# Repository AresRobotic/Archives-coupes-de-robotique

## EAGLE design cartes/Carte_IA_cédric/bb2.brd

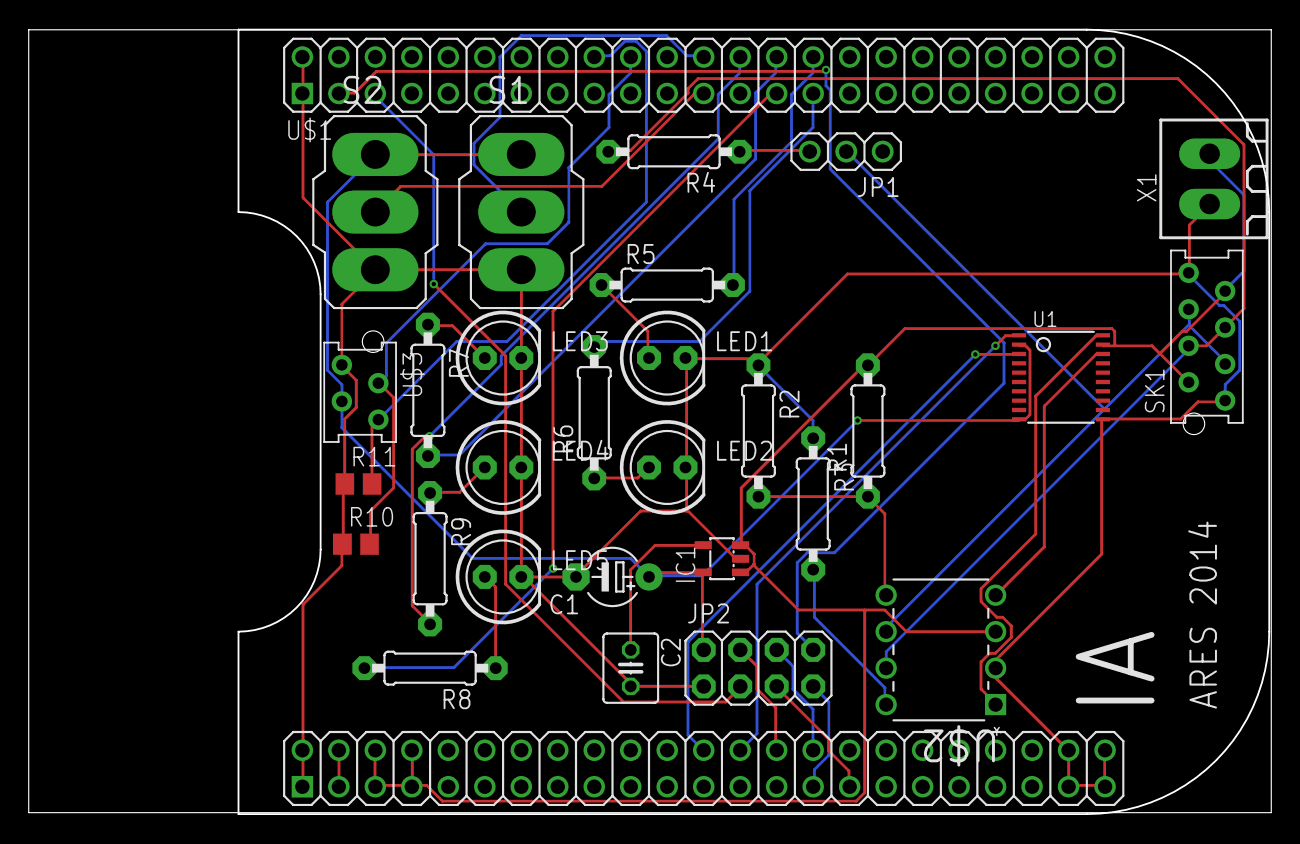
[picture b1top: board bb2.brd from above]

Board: 2 copper layers, 86.5 x 54.5 mm, 29 parts (0 on the bottom side), 34 nets.

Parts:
C1: 2.2u; E5-4
C2: 470p; C025-040X050
IC1: MIC5219BM5; SOT23-5
JP1: 1X03
JP2: 2X04
LED1, LED2, LED3, LED4, LED5: LED5MM
R1, R2, R5, R6, R7, R8, R9: 47k; 0207/9
R3: 4.7k; 0207/9
R4: 120; 0207/9
R10, R11: 10k; R0805
S1, S2: 320-916
SK1: AMP-215079-8
U1: TSSOP20
U$1: BEAGLEBONE_OUTLINE; BEAGLEBONE_SHIELD
U$2: MCP2551-E/P; DIP254P762X432-8
U$3: MMATCH-4-; AMP-215079-4
X1: 180G-2

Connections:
COULEUR: R11.2, U$1.18, U$3.4
DCAN1_RX: U1.3, U$1.70
DCAN1_TX: U1.1, U$1.72
GND: C1.-, C2.2, IC1.2, JP2.1, LED1.K, LED2.K, LED3.K, LED4.K, LED5.K, R2.1, R3.1, R10.1, R11.1, S1.3, S2.3, SK1.1, SK1.8, U1.11, U$1.1, U$1.2, U$1.47, U$1.48, U$1.89, U$1.90, U$1.91, U$1.92, U$2.2, U$3.1, X1.1
unnamed: R1.1, R2.2, U$2.5
unnamed: JP1.3, R4.1
unnamed: R3.2, U$2.8
unnamed: C2.1, IC1.4
unnamed: R5.2, U$1.30
unnamed: R6.2, U$1.29
unnamed: R7.2, U$1.28
unnamed: R9.2, U$1.26
unnamed: LED5.A, R8.1
unnamed: S1.2, U$1.24
unnamed: S2.2, U$1.23
unnamed: R8.2, U$1.27
unnamed: JP1.2, SK1.3, SK1.6, U$2.6
unnamed: R4.2, SK1.4, SK1.5, U$2.7
unnamed: LED2.A, R6.1
unnamed: LED1.A, R5.1
unnamed: LED3.A, R7.1
unnamed: LED4.A, R9.1
RXD: U1.18, U$2.4
SPI_CE: JP2.3, U$1.5
SPI_CS: JP2.4, U$1.74
SPI_IRQ: JP2.8, U$1.3
SPI_MISO: JP2.7, U$1.75
SPI_MOSI: JP2.6, U$1.76
SPI_SCLK: JP2.5, U$1.77
TIRETTE: R10.2, U$1.20, U$3.2
TXD: U1.20, U$2.1
VDD: IC1.1, IC1.3, R1.2, SK1.2, SK1.7, U1.19, U$1.51, U$1.52, U$1.53, U$1.54, U$2.3, X1.2
VDD_3V3: C1.+, IC1.5, JP2.2, S1.1, S2.1, U1.2, U1.10, U$3.3
VDD_3V3EXP: U$1.49, U$1.50

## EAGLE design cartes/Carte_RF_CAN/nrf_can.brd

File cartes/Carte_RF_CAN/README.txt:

A vérifier et faire gerber
Théo 24/04 à 23h40

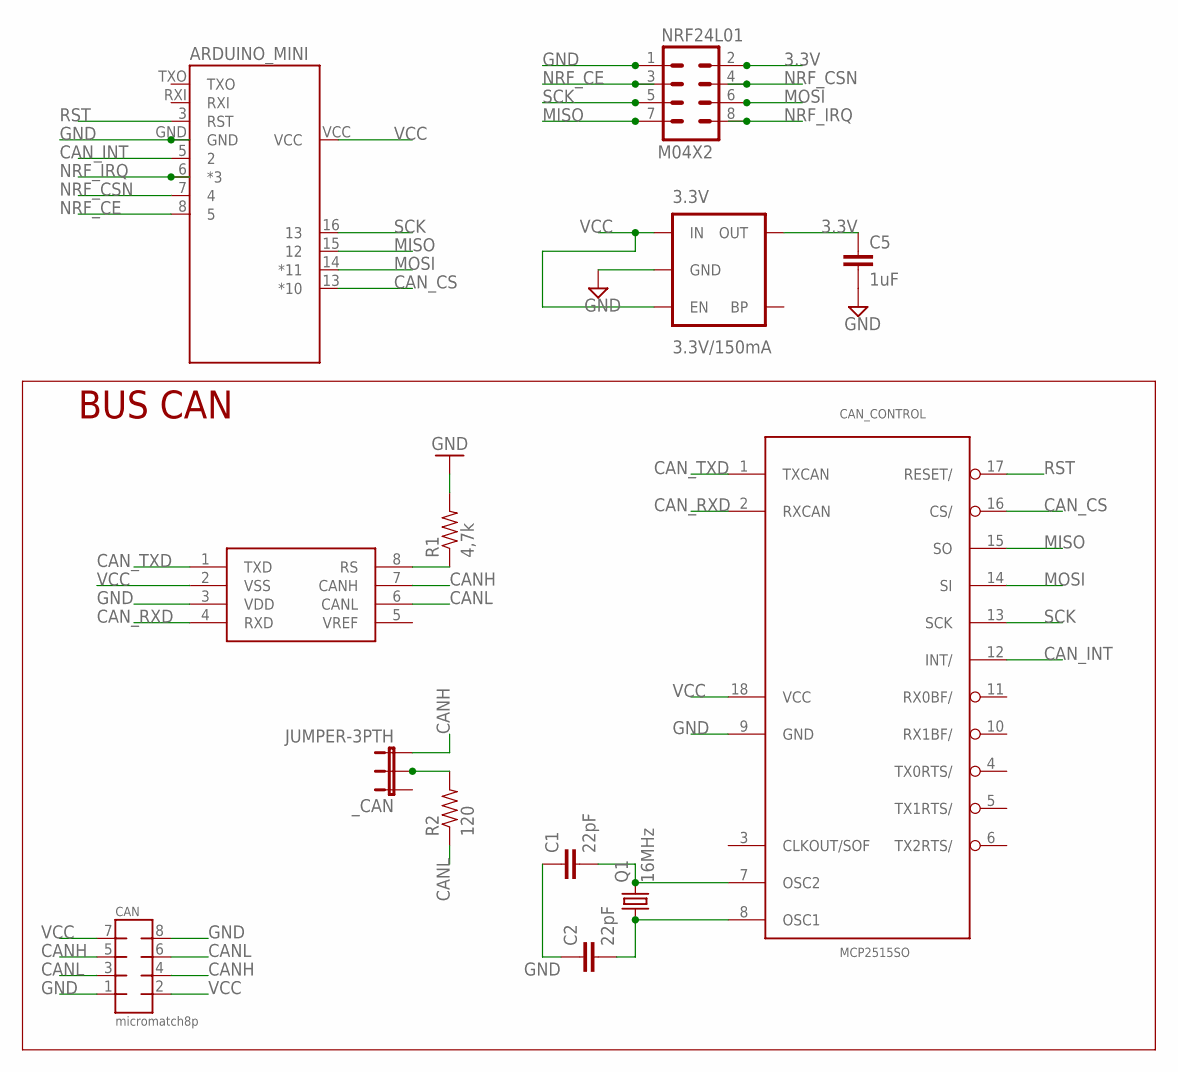
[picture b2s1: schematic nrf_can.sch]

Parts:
3.3V: 3.3V/150mA; SOT23-5
ARDUINO_MINI: ARDUINO_PRO_MININRF24L01; ARDUINO_PRO_MINI
C1, C2: 22pF; 0805
C5: 1uF; 0805
CAN: micromatch8p; AMP-215079-8
CAN_CONTROL: MCP2515SO; SO18L
NRF24L01: M04X2; 2X4
Q1: 16MHz; HC49/S
R1: 4,7k; 0805
R2: 120; 0805
TRANSCEIVER: MCP2551; SO08
_CAN: JUMPER-3PTH; 1X03

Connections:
3.3V: 3.3V.5 (OUT), C5.1, NRF24L01.2
CANH: CAN.4, CAN.5, TRANSCEIVER.7 (CANH), _CAN.3
CANL: CAN.3, CAN.6, R2.1, TRANSCEIVER.6 (CANL)
CAN_CS: ARDUINO_MINI.13 (*10), CAN_CONTROL.16 (CS/)
CAN_INT: ARDUINO_MINI.5 (2), CAN_CONTROL.12 (INT/)
CAN_RXD: CAN_CONTROL.2 (RXCAN), TRANSCEIVER.4 (RXD)
CAN_TXD: CAN_CONTROL.1 (TXCAN), TRANSCEIVER.1 (TXD)
GND: 3.3V.2 (GND), ARDUINO_MINI.GND, C1.1, C2.1, C5.2, CAN.1, CAN.8, CAN_CONTROL.9 (GND), NRF24L01.1, R1.2, TRANSCEIVER.3 (VDD)
MISO: ARDUINO_MINI.15 (12), CAN_CONTROL.15 (SO), NRF24L01.7
MOSI: ARDUINO_MINI.14 (*11), CAN_CONTROL.14 (SI), NRF24L01.6
unnamed: C1.2, CAN_CONTROL.7 (OSC2), Q1.2
unnamed: C2.2, CAN_CONTROL.8 (OSC1), Q1.1
unnamed: R1.1, TRANSCEIVER.8 (RS)
unnamed: R2.2, _CAN.2
NRF_CE: ARDUINO_MINI.8 (5), NRF24L01.3
NRF_CSN: ARDUINO_MINI.7 (4), NRF24L01.4
NRF_IRQ: ARDUINO_MINI.6 (*3), NRF24L01.8
RST: ARDUINO_MINI.3 (RST), CAN_CONTROL.17 (RESET/)
SCK: ARDUINO_MINI.16 (13), CAN_CONTROL.13 (SCK), NRF24L01.5
VCC: 3.3V.1 (IN), 3.3V.3 (EN), ARDUINO_MINI.VCC, CAN.2, CAN.7, CAN_CONTROL.18 (VCC), TRANSCEIVER.2 (VSS)

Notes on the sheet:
BUS CAN

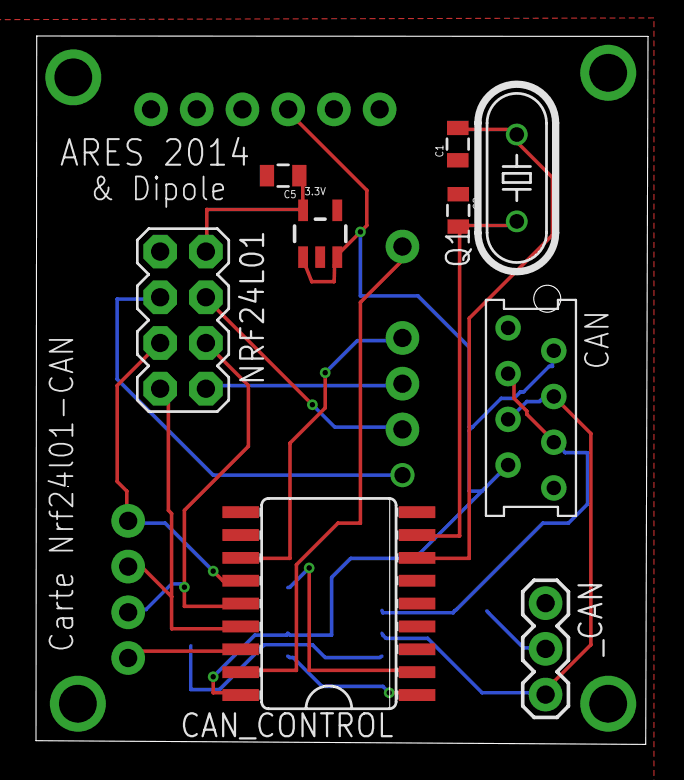
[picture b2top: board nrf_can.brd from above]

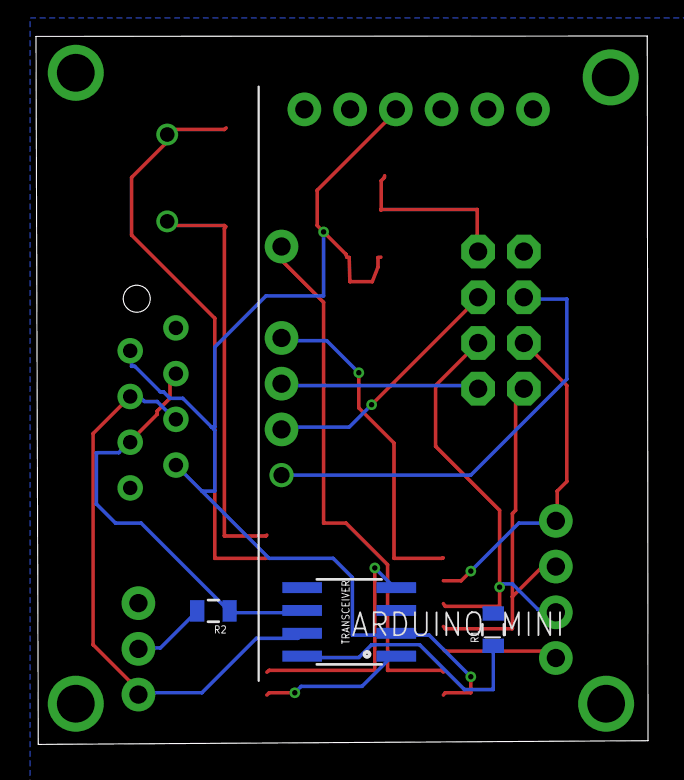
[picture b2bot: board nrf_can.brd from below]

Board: 2 copper layers, 34.0 x 39.4 mm, 13 parts (4 on the bottom side), 20 nets.

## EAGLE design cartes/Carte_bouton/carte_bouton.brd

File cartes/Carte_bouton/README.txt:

Modifié par Théo le 25/04 à 08:27 pour retourner le connecteur micromatch (au botom) et génrer le GERBER.
Prêt pour la production (x3)

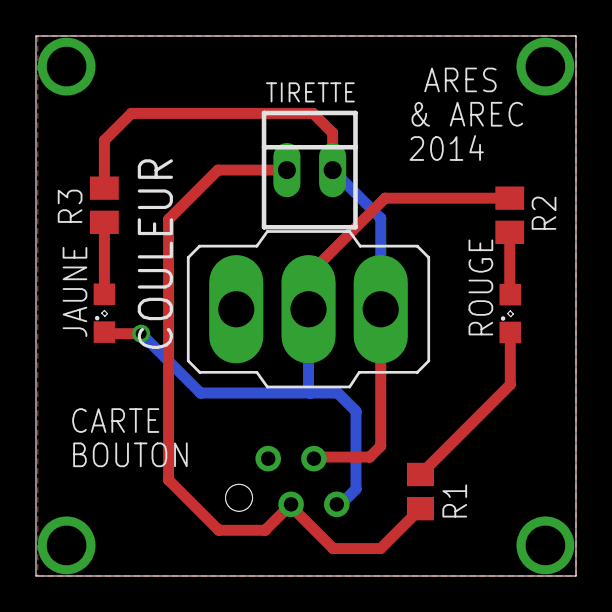
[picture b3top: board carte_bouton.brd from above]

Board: 2 copper layers, 30.0 x 30.0 mm, 8 parts (1 on the bottom side), 6 nets.

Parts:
CARTE_IA: MMATCH-4-; AMP-215079-4
COULEUR: 320-916
JAUNE: SML0805
R1: R0805
R2, R3: 1k; M0805
ROUGE: SML0805
TIRETTE: 22-23-2021

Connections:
+3V3: CARTE_IA.3, COULEUR.3, R3.2, TIRETTE.2
GND: CARTE_IA.1, COULEUR.1, R1.1, ROUGE.C
unnamed: CARTE_IA.4, COULEUR.2, JAUNE.C, R2.1
unnamed: R2.2, ROUGE.A
unnamed: JAUNE.A, R3.1
TIRETTE: CARTE_IA.2, R1.2, TIRETTE.1

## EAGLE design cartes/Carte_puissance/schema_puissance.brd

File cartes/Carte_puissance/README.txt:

*A vérifier et faire gerber
Théo 24/04 à 23h51

* Vérifié et sérigraphié par Théo le 25/05 à 8h40
A tirer x2 et si fonctionne parfaitement, à refaire x2 ou x3 (4 ou 5 au total)

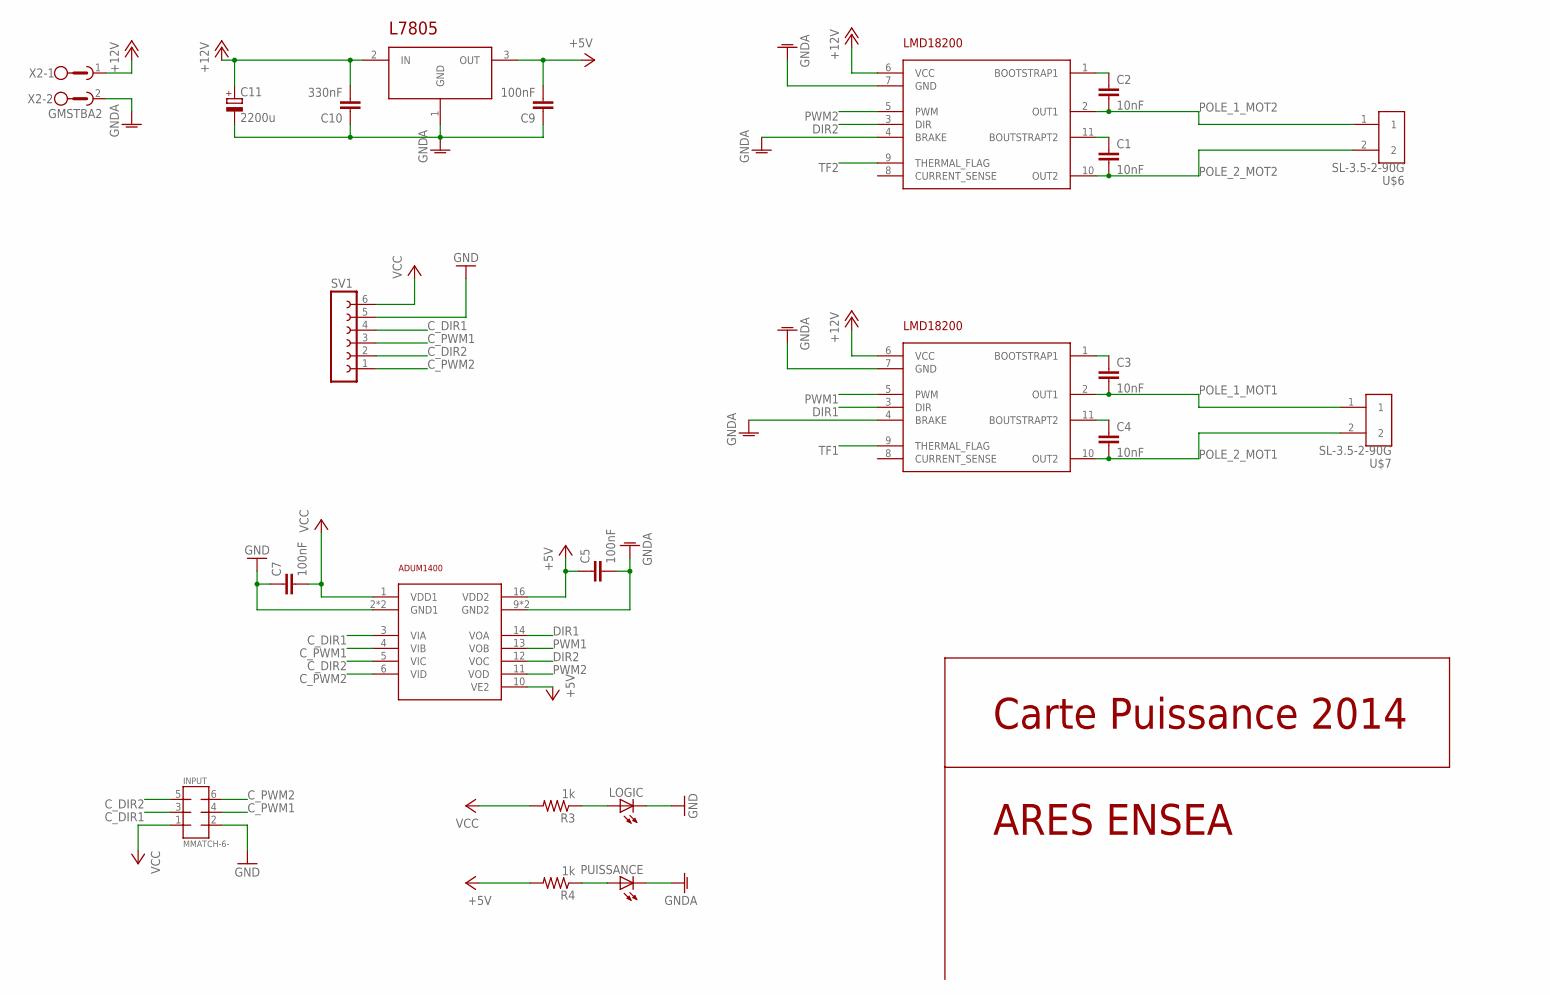
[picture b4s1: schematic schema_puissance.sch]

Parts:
C1, C2, C3, C4: 10nF; C0805
C5, C7, C9: 100nF; C0805
C10: 330nF; C0805
C11: 2200u; TT5D11
INPUT: MMATCH-6-; AMP-215079-6
LOGIC: LEDSML0805; SML0805
PUISSANCE: LEDSML0805; SML0805
R3, R4: 1k; M0805
SV1: FE06-1; FE06
U$1, U$2: LMD18200
U$3: ADUM1400S; SO-16W
U$5: L7805TO263; DPAK
U$6, U$7: SL-3.5-2-90G
X2: GMSTBA2

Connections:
+5V: C5.1, C9.2, R4.2, U$3.10 (VE2), U$3.16 (VDD2), U$5.3 (OUT)
+12V: C10.2, C11.+, U$1.6 (VCC), U$2.6 (VCC), U$5.2 (IN), X2.1
C_DIR1: INPUT.3 (5), SV1.4, U$3.3 (VIA); also elsewhere on the board
C_DIR2: INPUT.5 (7), SV1.2, U$3.5 (VIC); also elsewhere on the board
C_PWM1: INPUT.4 (6), SV1.3, U$3.4 (VIB); also elsewhere on the board
C_PWM2: INPUT.6 (8), SV1.1, U$3.6 (VID); also elsewhere on the board
DIR1: U$1.3 (DIR), U$3.14 (VOA)
DIR2: U$2.3 (DIR), U$3.12 (VOC)
GND: C7.1, INPUT.2 (4), LOGIC.C, SV1.5, U$3.2 (GND1), U$3.8 (GND1); also elsewhere on the board
GNDA: C5.2, C9.1, C10.1, C11.-, PUISSANCE.C, U$1.4 (BRAKE), U$1.7 (GND), U$2.4 (BRAKE), U$2.7 (GND), U$3.9 (GND2), U$3.15 (GND2), U$5.1 (GND), X2.2
unnamed: C1.1, U$2.11 (BOUTSTRAPT2)
unnamed: PUISSANCE.A, R4.1
unnamed: C2.1, U$2.1 (BOOTSTRAP1)
unnamed: LOGIC.A, R3.1
unnamed: C3.1, U$1.1 (BOOTSTRAP1)
unnamed: C4.1, U$1.11 (BOUTSTRAPT2)
POLE_1_MOT1: C3.2, U$1.2 (OUT1), U$7.1
POLE_1_MOT2: C2.2, U$2.2 (OUT1), U$6.1
POLE_2_MOT1: C4.2, U$1.10 (OUT2), U$7.2
POLE_2_MOT2: C1.2, U$2.10 (OUT2), U$6.2
PWM1: U$1.5 (PWM), U$3.13 (VOB)
PWM2: U$2.5 (PWM), U$3.11 (VOD)
TF1: U$1.9 (THERMAL_FLAG)
TF2: U$2.9 (THERMAL_FLAG)
VCC: C7.2, INPUT.1 (3), R3.2, SV1.6, U$3.1 (VDD1); also elsewhere on the board

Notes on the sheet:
Carte Puissance 2014
ARES ENSEA

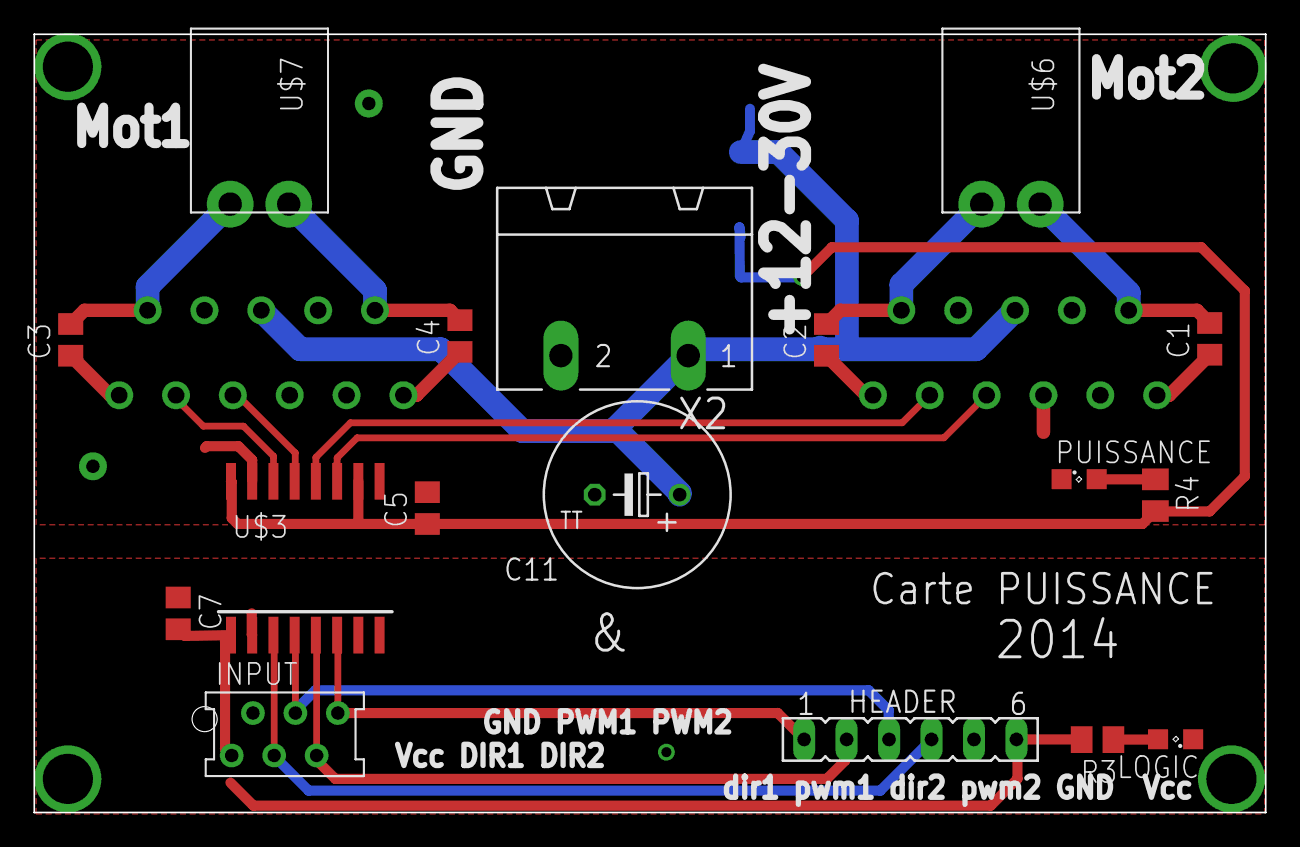
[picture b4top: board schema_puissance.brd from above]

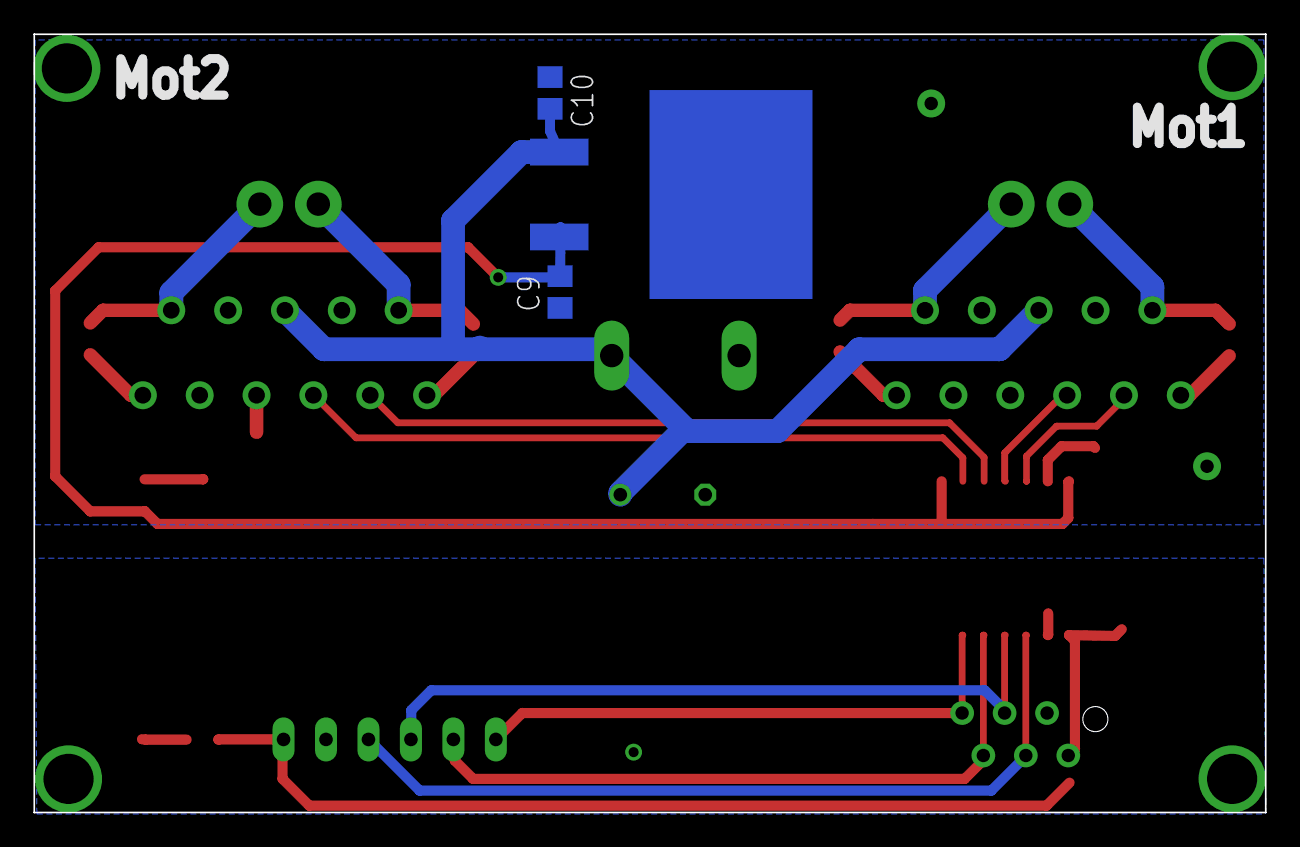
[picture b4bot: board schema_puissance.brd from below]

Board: 2 copper layers, 73.7 x 46.6 mm, 22 parts (3 on the bottom side), 23 nets.

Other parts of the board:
HEADER: FE06

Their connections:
C_DIR1: HEADER.4; also elsewhere on the board
C_DIR2: HEADER.2; also elsewhere on the board
C_PWM1: HEADER.3; also elsewhere on the board
C_PWM2: HEADER.1; also elsewhere on the board
GND: HEADER.5; also elsewhere on the board
VCC: HEADER.6; also elsewhere on the board

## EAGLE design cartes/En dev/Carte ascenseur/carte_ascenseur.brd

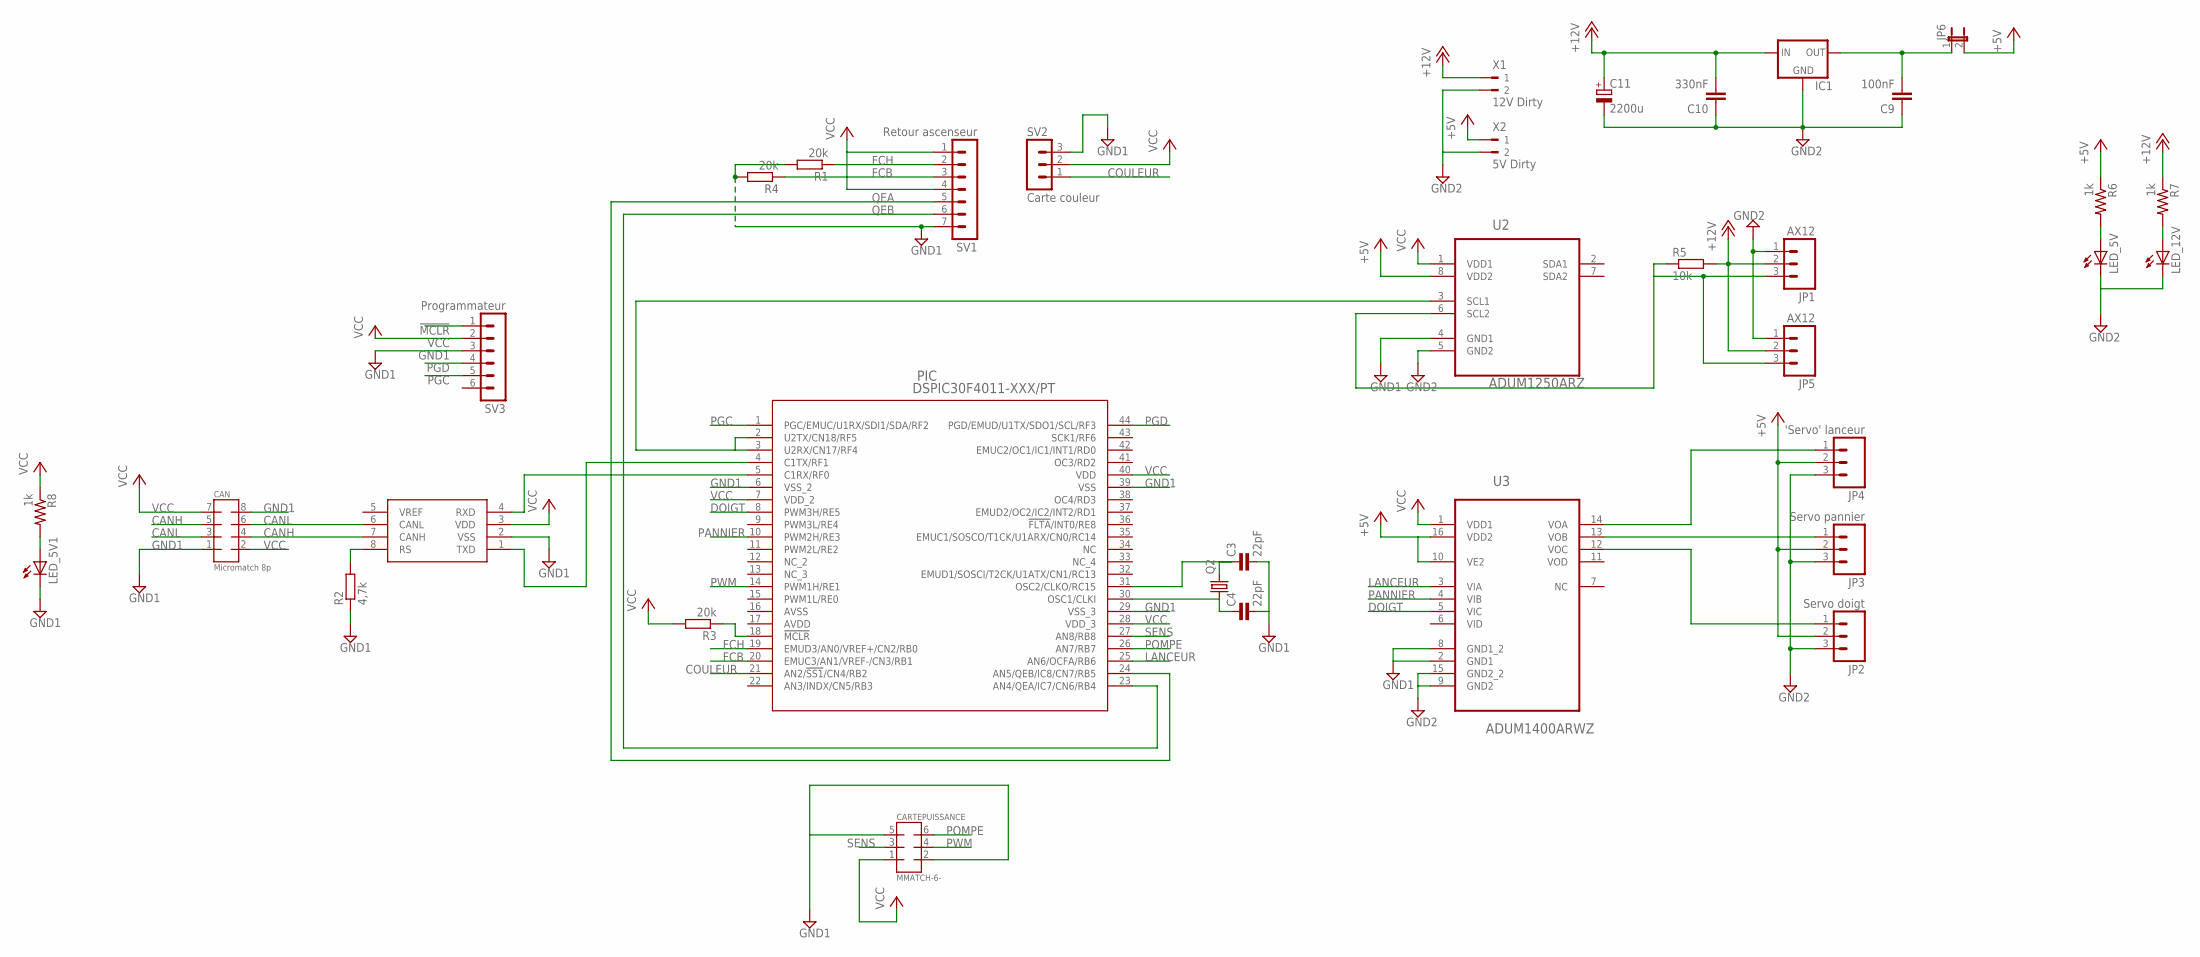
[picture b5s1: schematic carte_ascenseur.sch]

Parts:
C3, C4: 22pF; 0805
C9: 100nF; C0805
C10: 330nF; C0805
C11: 2200u; TT5D11
CAN: Micromatch 8p; AMP-215079-8
CARTEPUISSANCE: MMATCH-6-; AMP-215079-6
IC1: V_REG_78XX-TO-220; TO-220-ALT
JP1, JP5: AX12; MOLEX-1X3
JP2: Servo doigt; 1X03
JP3: Servo pannier; 1X03
JP4: 'Servo' lanceur; 1X03
JP6: JP1E; JP1
LED_5V, LED_5V1, LED_12V: LEDCHIPLED_0805; CHIPLED_0805
PIC: DSPIC30F4011-XXX/PT; TQFP44_MC
Q2: CRYSTALHC49S; HC49/S
R1, R3, R4: 20k; M0805
R2: 4,7k; M0805
R5: 10k; M0805
R6, R7, R8: 1k; 0805
SV1: Retour ascenseur; MA07-1
SV2: Carte couleur; MA03-1
SV3: Programmateur; MA06-1
U1: MCP2551; SO08
U2: ADUM1250ARZ; SOIC127P600X175-8N
U3: ADUM1400ARWZ; SOIC127P1032X265-16N
X1: 12V Dirty; 90-2
X2: 5V Dirty; 90-2

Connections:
!MCLR!: PIC.18 (!MCLR!), R3.1, SV3.1
+5V: JP2.2, JP3.2, JP4.2, JP6.2, R6.1, U2.8 (VDD2), U3.10 (VE2), U3.16 (VDD2), X2.1
+12V: C10.2, C11.+, IC1.IN, JP1.2, JP5.2, R5.2, R7.1, X1.1; also elsewhere on the board
CANH: CAN.4, CAN.5, U1.7 (CANH)
CANL: CAN.3, CAN.6, U1.6 (CANL)
COULEUR: PIC.21 (AN2/!SS1!/CN4/RB2), SV2.1
C_S2: PIC.38 (OC4/RD3), SV2.5
C_S3: PIC.37 (EMUD2/OC2/IC2/INT2/RD1), SV2.4
DOIGT: PIC.8 (PWM3H/RE5), U3.5 (VIC)
FCB: PIC.20 (EMUC3/AN1/VREF-/CN3/RB1), R4.1, SV1.3
FCH: PIC.19 (EMUD3/AN0/VREF+/CN2/RB0), R1.1, SV1.2
GND1: C3.2, C4.2, CAN.1, CAN.8, CARTEPUISSANCE.2 (4), CARTEPUISSANCE.5 (7), LED_5V1.C, PIC.6 (VSS_2), PIC.29 (VSS_3), PIC.39 (VSS), R1.2, R2.1, R4.2, SV1.7, SV2.3, SV3.3, U1.2 (VSS), U2.4 (GND1), U3.2 (GND1), U3.8 (GND1_2)
GND2: C9.1, C10.1, C11.-, IC1.GND, JP1.1, JP2.3, JP3.3, JP4.3, JP5.1, LED_5V.C, LED_12V.C, U2.5 (GND2), U3.9 (GND2), U3.15 (GND2_2), X1.2, X2.2; also elsewhere on the board
LANCEUR: PIC.25 (AN6/OCFA/RB6), U3.3 (VIA)
unnamed: PIC.4 (C1TX/RF1), U1.1 (TXD)
unnamed: LED_5V.A, R6.2
unnamed: PIC.5 (C1RX/RF0), U1.4 (RXD)
unnamed: R2.2, U1.8 (RS)
unnamed 19: C9.2, IC1.OUT, JP6.1; also elsewhere on the board
unnamed: PIC.2 (U2TX/CN18/RF5), PIC.3 (U2RX/CN17/RF4), U2.3 (SCL1)
unnamed: JP4.1, U3.14 (VOA)
unnamed: JP3.1, U3.13 (VOB)
unnamed: JP2.1, U3.12 (VOC)
unnamed: LED_12V.A, R7.2
unnamed: LED_5V1.A, R8.2
unnamed: C3.1, PIC.31 (OSC2/CLKO/RC15), Q2.2
unnamed: JP1.3, JP5.3, R5.1, U2.6 (SCL2)
unnamed: C4.1, PIC.30 (OSC1/CLKI), Q2.1
PANNIER: PIC.10 (PWM2H/RE3), U3.4 (VIB)
PGC: PIC.1 (PGC/EMUC/U1RX/SDI1/SDA/RF2), SV3.5
PGD: PIC.44 (PGD/EMUD/U1TX/SDO1/SCL/RF3), SV3.4
POMPE: CARTEPUISSANCE.6 (8), PIC.26 (AN7/RB7)
PWM: CARTEPUISSANCE.4 (6), PIC.14 (PWM1H/RE1)
QEA: PIC.24 (AN5/QEB/IC8/CN7/RB5), SV1.5
QEB: PIC.23 (AN4/QEA/IC7/CN6/RB4), SV1.6
SENS: CARTEPUISSANCE.3 (5), PIC.27 (AN8/RB8)
VCC: CAN.2, CAN.7, CARTEPUISSANCE.1 (3), PIC.7 (VDD_2), PIC.28 (VDD_3), PIC.40 (VDD), R3.2, R8.1, SV1.1, SV1.4, SV2.2, SV3.2, U1.3 (VDD), U2.1 (VDD1), U3.1 (VDD1)

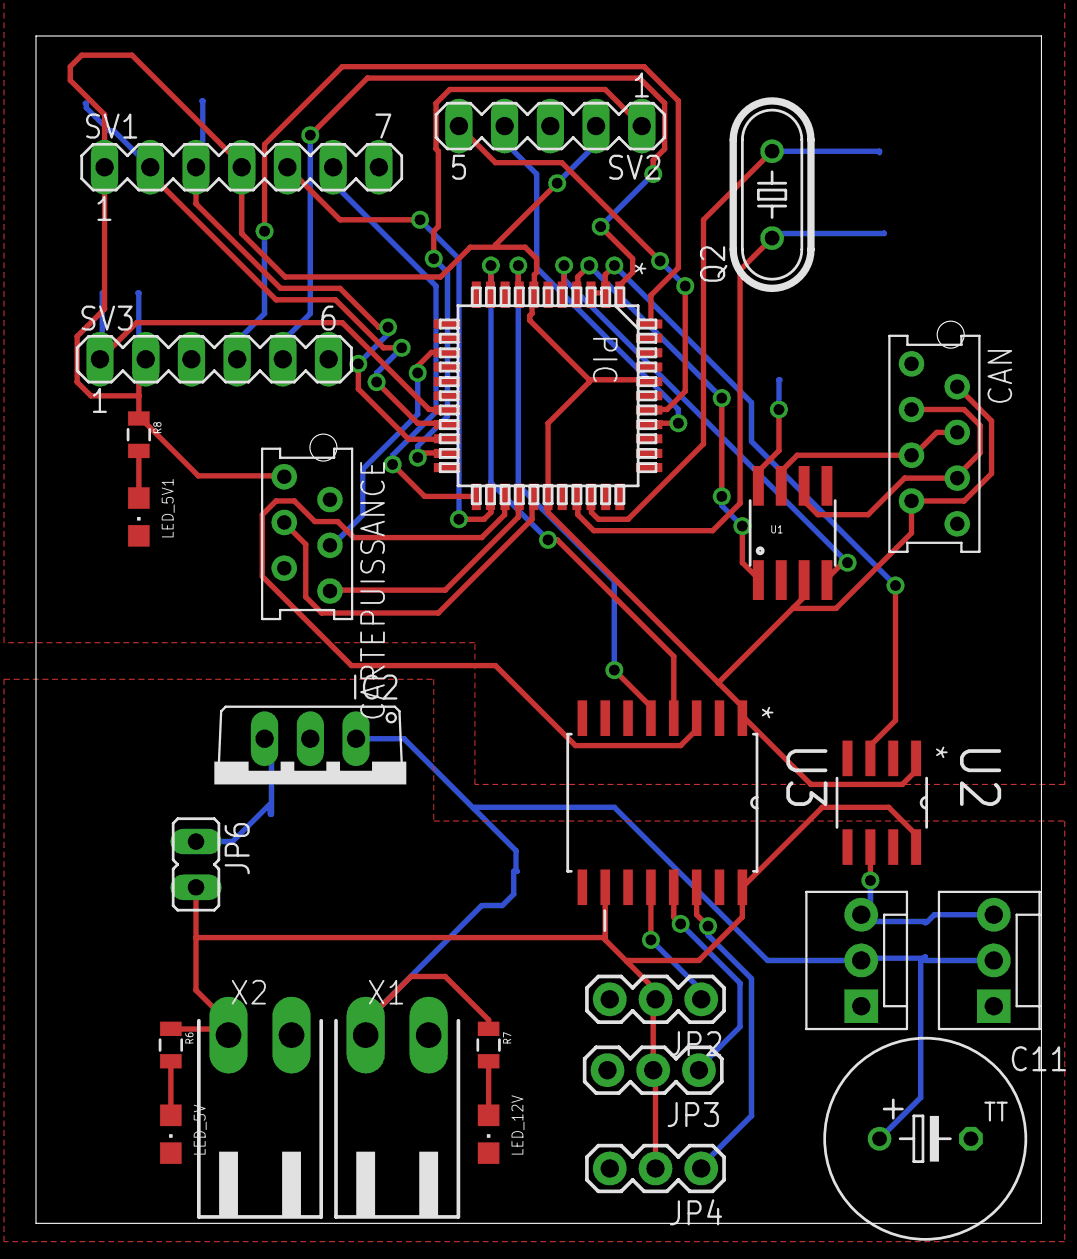
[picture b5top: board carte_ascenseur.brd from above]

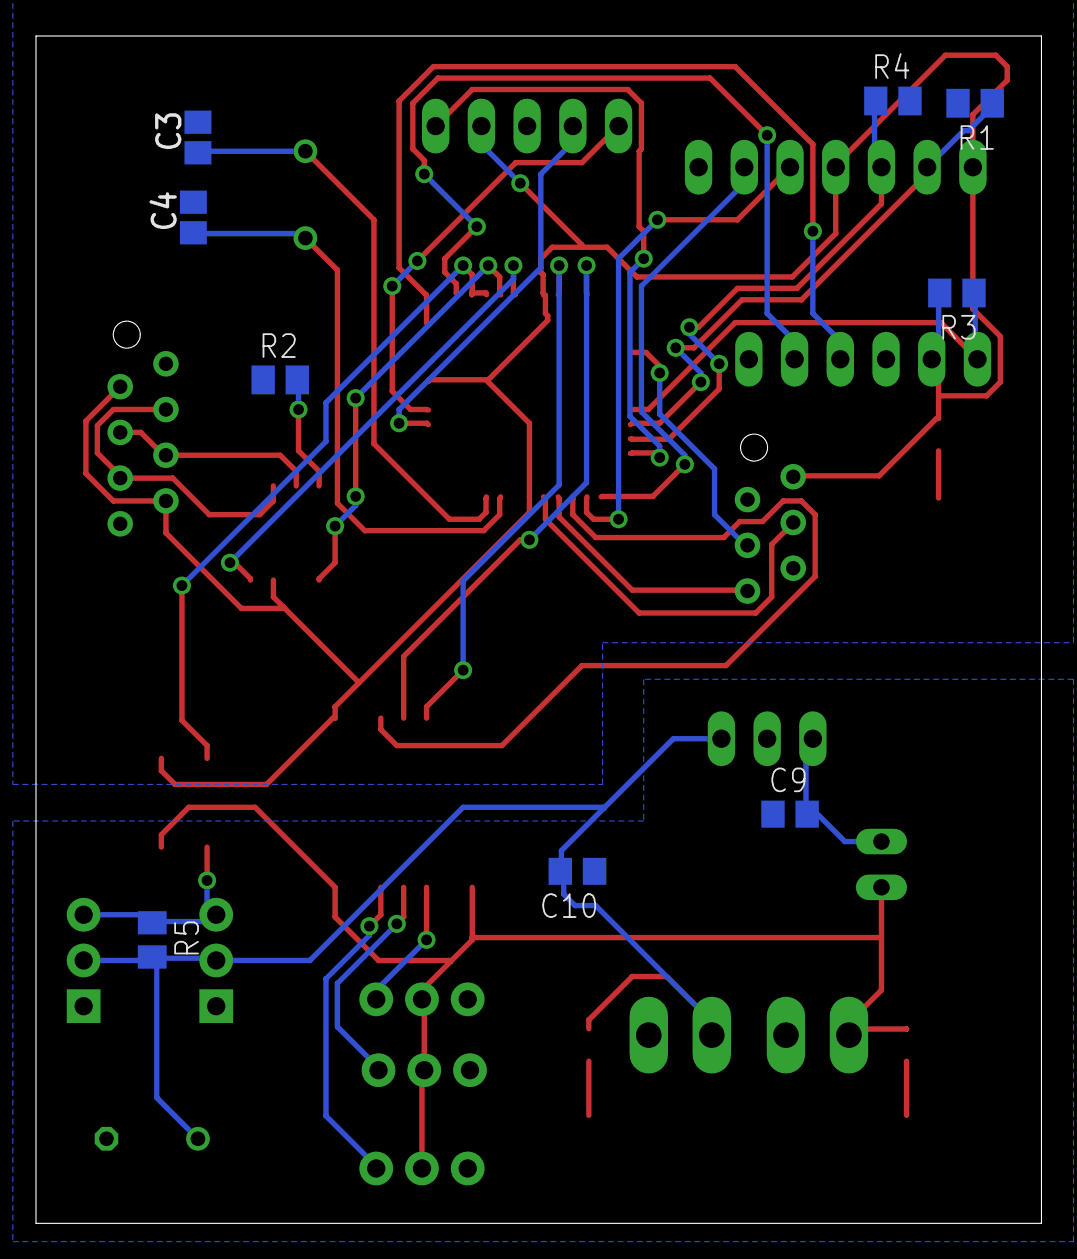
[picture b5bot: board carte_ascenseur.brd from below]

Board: 2 copper layers, 55.9 x 66.0 mm, 35 parts (9 on the bottom side), 37 nets.

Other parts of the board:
IC2: 7805TV; TO220V

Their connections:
+12V: IC2.1; also elsewhere on the board
GND2: IC2.2; also elsewhere on the board
unnamed 19: IC2.3; also elsewhere on the board

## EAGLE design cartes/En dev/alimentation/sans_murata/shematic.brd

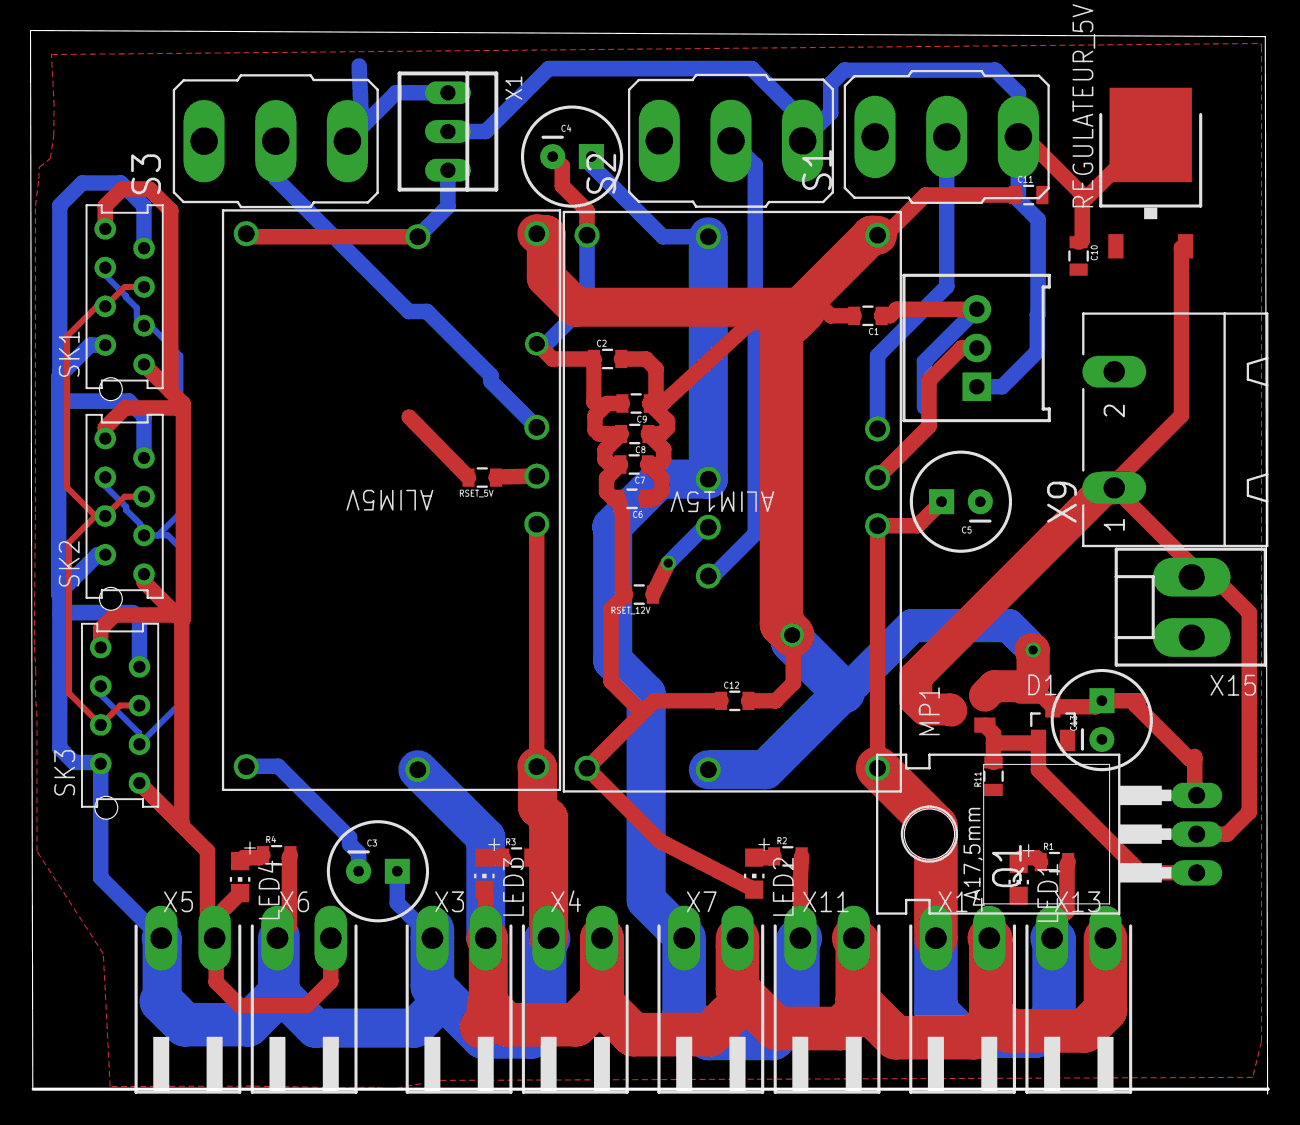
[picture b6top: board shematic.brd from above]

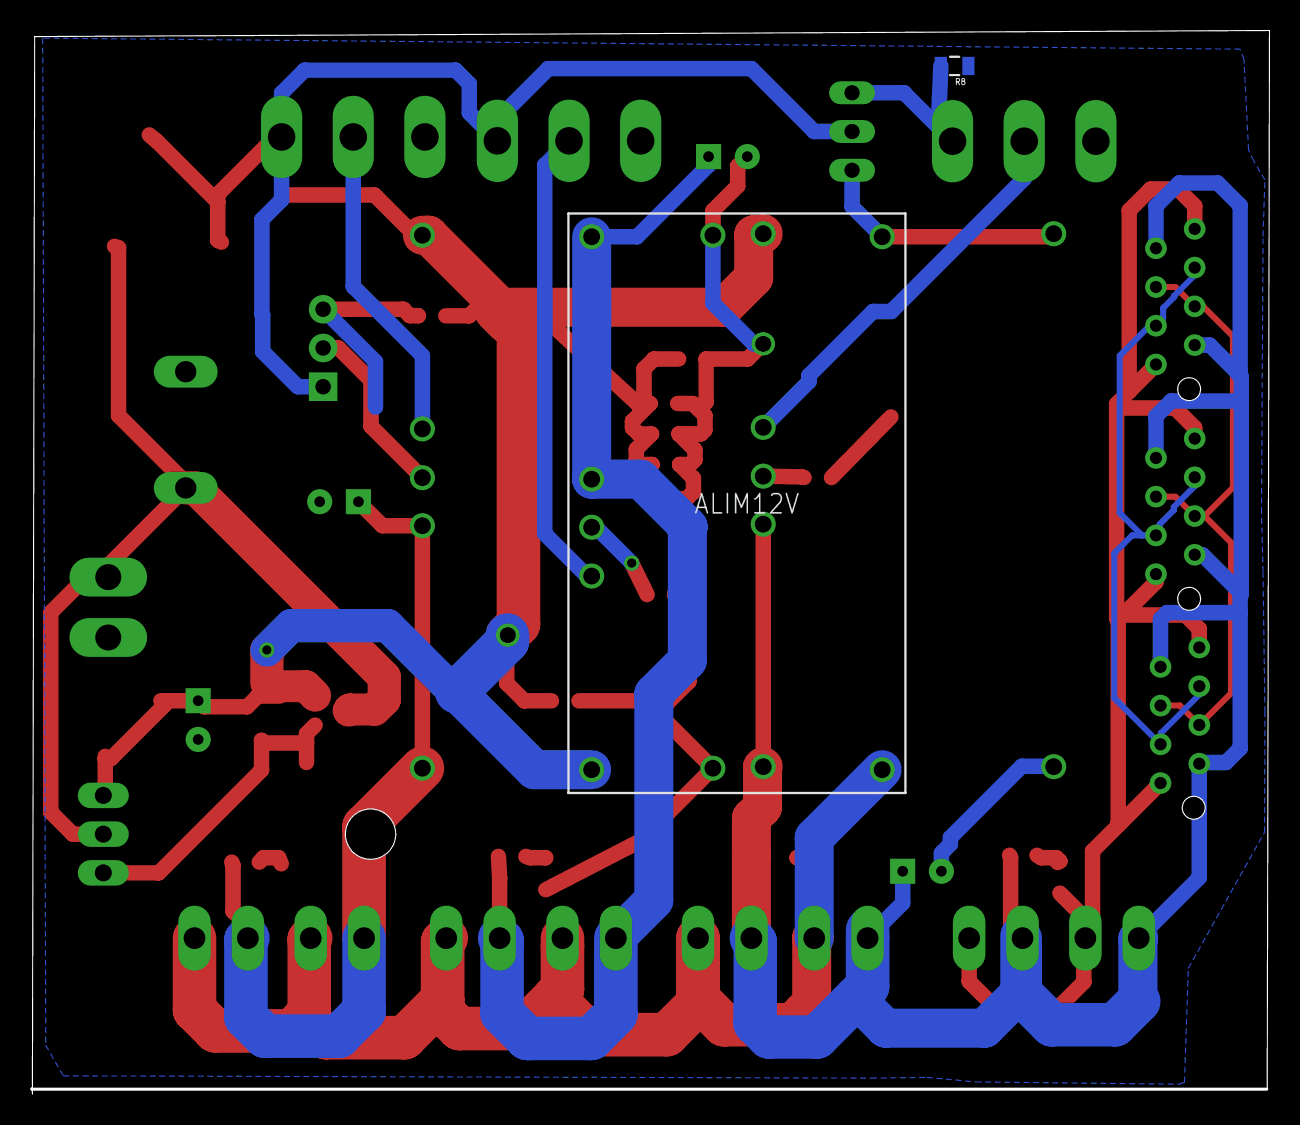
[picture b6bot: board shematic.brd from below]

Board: 2 copper layers, 81.1 x 69.8 mm, 50 parts (2 on the bottom side), 22 nets.

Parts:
ALIM5V, ALIM12V: PTN78020WAH; EUK7
ALIM15V: PTN78020HAH; EUK7
C1, C2, C12: 2.2uF; 0805
C3, C4, C5: 330uF; CPOL-RADIAL-100UF-25V
C6, C7, C8, C9: 4.7uF; 0805
C10: 0.1uF; 0805
C11: 0.33uF; 0805
C13: CPOL-RADIAL-100UF-25V
D1: SOT23
LED1, LED2, LED3, LED4: CHIP-LED0805
MAX=100K: Rset_15v; 3386U
MP1: SOT23
Q1: TO220BH
R1, R2: 2k; 0805
R3, R4: 820; 0805
R8: 1k; 0805
R11: 100k; 0805
REGULATEUR_5V: MC33269D-5.0; DPACK
RSET_5V: 21k; 0805
RSET_12V: 734; 0805
S1, S2, S3: M9040P
SK1, SK2, SK3: AMP-215079-8
X1: 22-23-2031
X3: OUT1_5v; 90-2
X4: OUT2_5v; 90-2
X5: OUT1_T5V; 90-2
X6: OUT2_T5v; 90-2
X7: OUT1_12v; 90-2
X9: IN_batteries; GMSTBA2
X11: OUT2_12v; 90-2
X13: OUT2_15v; 90-2
X14: OUT1_15v; 90-2
X15: prise_Voltmetre; KK-156-2

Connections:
ADJUST_5V: ALIM5V.4, RSET_5V.1
ADJUST_12V: ALIM12V.4, RSET_12V.1
ADJUST_15V: ALIM15V.4, MAX=100K.2
BAT: MP1.3, Q1.D, REGULATEUR_5V.3, X9.1, X15.2
CANH: SK1.4, SK1.5, SK2.4, SK2.5, SK3.4, SK3.5
CANL: SK1.3, SK1.6, SK2.3, SK2.6, SK3.3, SK3.6
GND: ALIM5V.1, ALIM5V.7, ALIM12V.1, ALIM12V.7, ALIM15V.1, ALIM15V.7, C1.1, C2.1, C3.2, C4.2, C5.2, C6.2, C7.2, C8.2, C9.2, C10.2, C11.2, C12.1, C13.2, LED1.C, LED2.C, LED3.C, MAX=100K.3, R8.1, R11.1, REGULATEUR_5V.1, RSET_5V.2, RSET_12V.2, S1.1, S2.1, S3.1, X1.3, X3.2, X4.2, X7.2, X9.2, X11.2, X13.2, X14.2, X15.1
GND_T: LED4.C, SK1.1, SK1.8, SK2.1, SK2.8, SK3.1, SK3.8, X5.2, X6.2
GRILLE: D1.1, MP1.1, Q1.G, R11.2
unnamed: LED1.A, R1.1
unnamed: LED2.A, R2.1
unnamed: LED3.A, R3.1
unnamed: LED4.A, R4.1
OUT_5V: ALIM5V.5, ALIM5V.6, C3.1, R3.2, R4.2, SK1.2, SK1.7, SK2.2, SK2.7, SK3.2, SK3.7, X3.1, X4.1, X5.1, X6.1
OUT_12V: ALIM12V.5, ALIM12V.6, C4.1, R2.2, X7.1, X11.1
OUT_15V: ALIM15V.5, ALIM15V.6, C5.1, R1.2, X13.1, X14.1
OUT_INTERR_1: ALIM15V.3, S1.2
OUT_INTERR_2: ALIM12V.3, S2.2
OUT_INTERR_3: ALIM5V.3, S3.2
OUT_MASTER_INTERR: R8.2, S3.3, X1.1
OUT_REG: C10.1, MAX=100K.1, REGULATEUR_5V.2, S1.3, S2.3, X1.2
VBAT: ALIM5V.2, ALIM12V.2, ALIM15V.2, C1.2, C2.2, C6.1, C7.1, C8.1, C9.1, C11.1, C12.2, C13.1, D1.3, MP1.2, Q1.S

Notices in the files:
parts and their libraries:
SparkFun-DigitalIC: Licensing: CC v3.0 Share-Alike You are welcome to use this library for commercial purposes.
